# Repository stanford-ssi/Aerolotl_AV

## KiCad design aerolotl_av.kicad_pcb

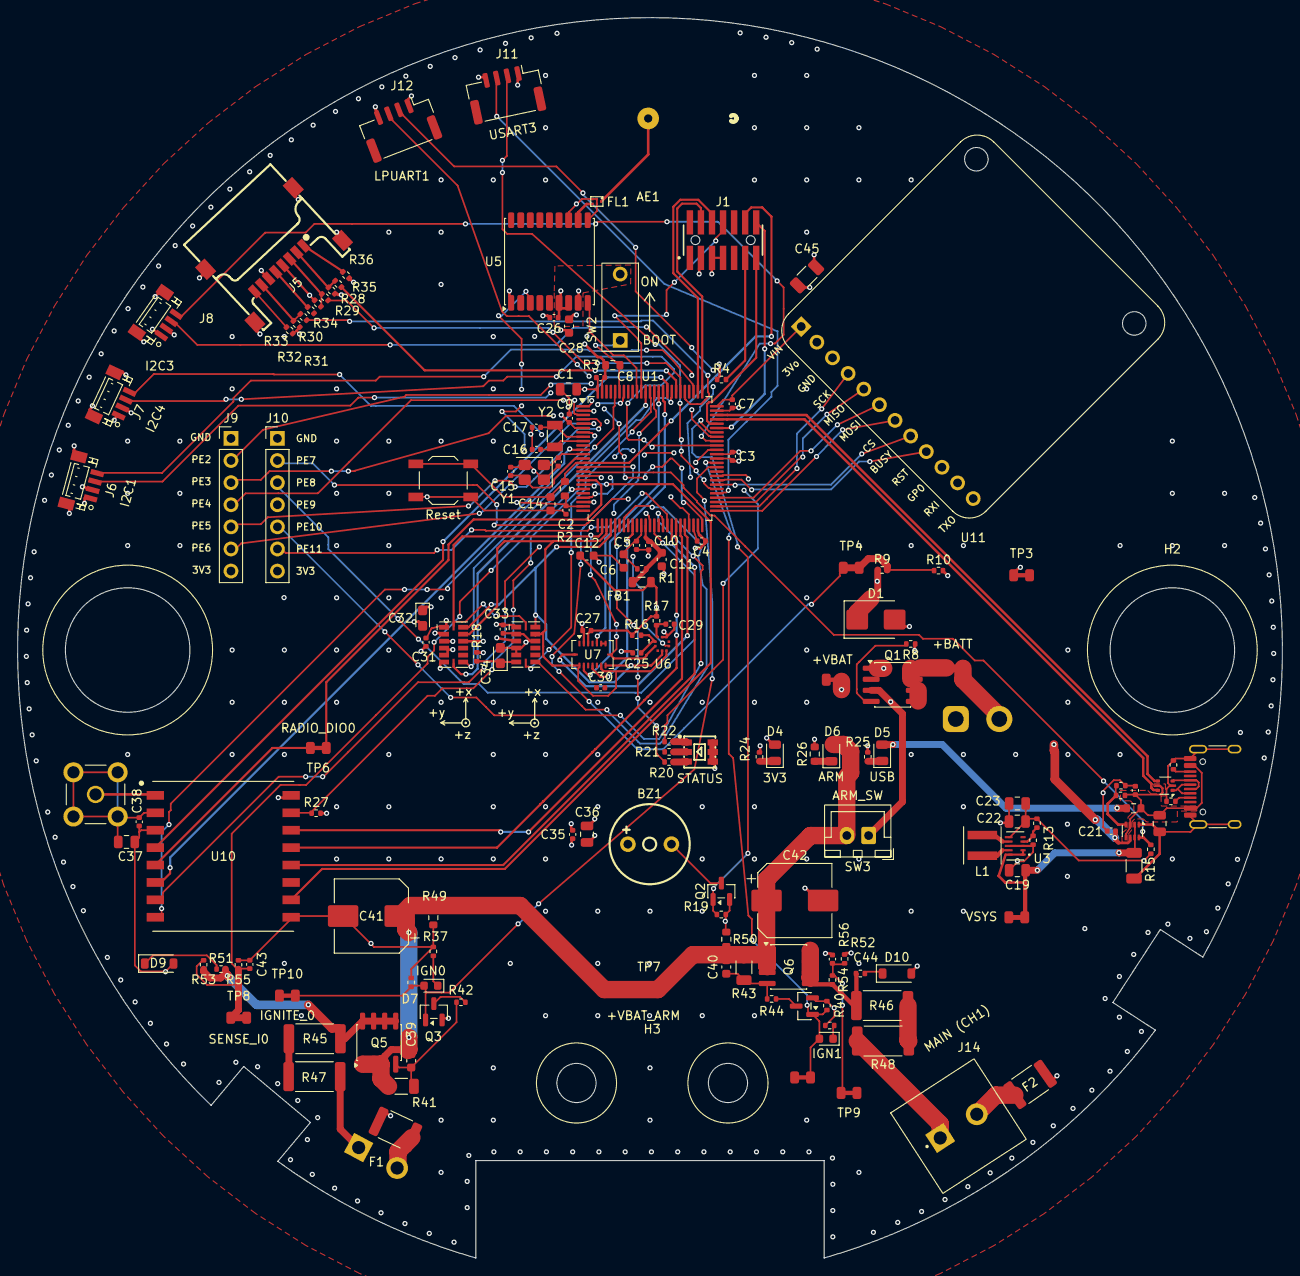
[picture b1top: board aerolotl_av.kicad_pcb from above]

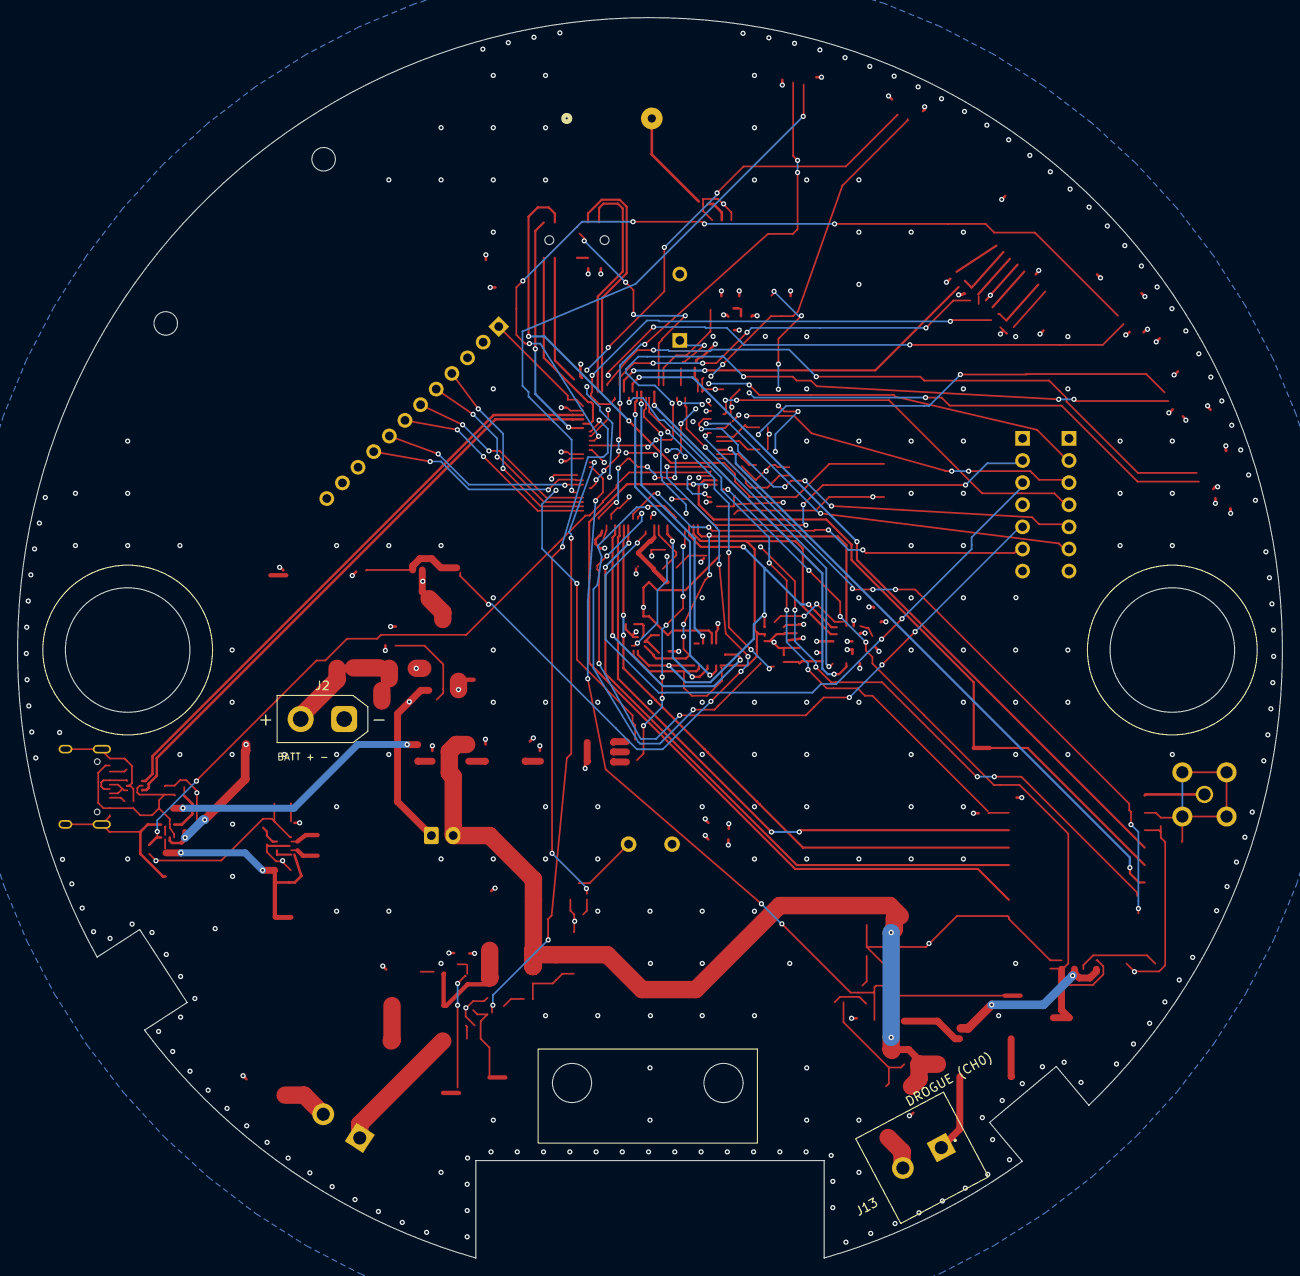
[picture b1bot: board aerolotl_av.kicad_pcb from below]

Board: 4 copper layers, 145.3 x 142.5 mm, 166 parts (2 on the bottom side), 134 nets.

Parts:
AE1: GP.1575.18.4.A.02; ANT_GP.1575.18.4.A.02_TAL
BZ1: HNB09A03; BUZ-TH_BD9.0-P5.00-D0.6-FD
C1: 4u7; C_0805_2012Metric
C2, C3, C4, C5, C7, C8, C9, C25, C26, C27, C29, C30, C31, C33, C35, C38, C43, C44: 100n; C_0402_1005Metric
C6, C11, C12: 1u; C_0603_1608Metric
C10: 10n; C_0402_1005Metric
C13, C15: 15p; C_0402_1005Metric
C14: 100n; C_0603_1608Metric
C16, C17: 4.7p; C_0402_1005Metric
C18, C19, C37: 10u; C_0805_2012Metric
C20, C21: 1u; C_0402_1005Metric
C22, C23, C36: 22u; C_0805_2012Metric
C24: 100u; C_1206_3216Metric
C28: 10u; C_0603_1608Metric
C32, C34: 1u; CP_EIA-2012-12_Kemet-R
C39, C40: 150n; C_0603_1608Metric
C41, C42: 330u; CP_Elec_8x10
C45: 47u; C_1206_3216Metric
D1: SMBJ5.0A; D_SMB
D2: STATUS; LED-SMD_RS-3535MWAR-2JYJY-J
D4: 3V3; LED_0805_2012Metric
D5: USB; LED_0805_2012Metric
D6: ARM; LED_0805_2012Metric
D7: IGN0; LED_0603_1608Metric
D8: IGN1; LED_0603_1608Metric
D9, D10: 1N4148W; D_SOD-123
F1, F2: 1812L150/24MR; Fuse_1812_4532Metric
FB1: 100; L_0805_2012Metric
FL1: B39162B4300F210; FILTER-SMD_5P-L1.4-W1.1_RSFPXXXXD
H1, H2: 3/8in rod; MountingHole_3-8in_Grommet_Heyco_G1123_D14.3mm
H3: TeleMetrum sled; TeleMetrum_Sled_Mount_2xM4
J1: SWD; STDC14_SAMTEC_FTSH-107-01-L-DV-K-A
J2: Battery (ext.); AMASS_XT30UPB-M_1x02_P5.0mm_Vertical
J3: USB_C_Receptacle_USB2.0_16P; USB_C_Receptacle_HRO_TYPE-C-31-M-12
J4: SMA; SMA_BAT-Wireless_BWSMA-KE-Z001_Vertical
J5: TF-102-15_SD_read; TF-SMD_TF-102-15
J6: I2C1; StemmaQT
J7: I2C4; StemmaQT
J8: I2C3; StemmaQT
J9: GPIO_PE2-PE6; PinHeader_1x07_P2.54mm_Vertical
J10: GPIO_PE7-PE11; PinHeader_1x07_P2.54mm_Vertical
J11: USART3; JST_GH_BM04B-GHS-TBT_1x04-1MP_P1.25mm_Vertical
J12: LPUART1; JST_GH_BM04B-GHS-TBT_1x04-1MP_P1.25mm_Vertical
J13, J14: WJ128V-5.0-2P; TerminalBlock_Kangnex_WJ128V-5.0-2P_C8269
L1: 0.47u; L_Coilcraft_XxL4020
Q1, Q5, Q6: DMP2022LSS-13; SOIC-8_3.9x4.9mm_P1.27mm
Q2, Q3, Q4: AO3400A; SOT-23
R1: 47; R_0402_1005Metric
R2, R3: 10k; R_0603_1608Metric
R4, R22, R42, R44: 100; R_0402_1005Metric
R5, R6: 5k1; R_0402_1005Metric
R7: 0R; R_0603_1608Metric
R8: 100k; R_0402_1005Metric
R9, R12, R15, R27, R32, R33, R34, R35, R36, R51, R52, R55, R56: 10k; R_0402_1005Metric
R10: 22k; R_0402_1005Metric
R11: 33k; R_0402_1005Metric
R13: 511k; R_0402_1005Metric
R14: 91k; R_0402_1005Metric
R16, R17, R18, R28, R29, R30, R31: 10; R_0402_1005Metric
R19: 3k3; R_0402_1005Metric
R20: 270; R_0402_1005Metric
R21, R37, R38: 330; R_0402_1005Metric
R24: 470; R_0402_1005Metric
R25: 910; R_0402_1005Metric
R26: 330; R_0603_1608Metric
R39, R40: 8k2; R_0402_1005Metric
R41, R43: 10k; R_1206_3216Metric
R45, R46, R47, R48: 1R; R_2512_6332Metric
R49, R50: 3k3; R_0603_1608Metric
R53, R54: 4.7k; R_0402_1005Metric
SW1: Reset; SW_SPST_TL3342
SW2: BOOT; SW_DIP_SPSTx01_Kingtek_DSWB01LHGET_W7.62mm
SW3: ARM_SW; JST_XH_B2B-XH-A_1x02_P2.50mm_Vertical
TP1: +BATT; TestPoint_KOA_RCTCTE_2.0x1.25mm
TP2: +VBAT; TestPoint_KOA_RCTCTE_2.0x1.25mm
TP3: +3V3; TestPoint_KOA_RCTCTE_2.0x1.25mm
TP4: VOLT_SENSE; TestPoint_KOA_RCTCTE_2.0x1.25mm
TP5: VSYS; TestPoint_KOA_RCTCTE_2.0x1.25mm
TP6: RADIO_DIO0; TestPoint_KOA_RCTCTE_2.0x1.25mm
TP7: +VBAT_ARM; TestPoint_KOA_RCTCTE_2.0x1.25mm
TP8: SENSE_I0; TestPoint_KOA_RCTCTE_2.0x1.25mm
TP9: SENSE_I1; TestPoint_KOA_RCTCTE_2.0x1.25mm
TP10: IGNITE_0; TestPoint_KOA_RCTCTE_2.0x1.25mm
TP11: IGNITE_1; TestPoint_KOA_RCTCTE_2.0x1.25mm
U1: STM32G473VET6; LQFP-100_14x14mm_P0.5mm
U2: USBLC6-2P6; SOT-666
U3: TPS63802DLAR; TI_VSON-HR-10_2x3mm_P0.5mm_DLA0010A
U4: TPS2116DRL; SOT-583-8
U5: MAX-M10S; ublox_MAX
U6: BMP581; LGA-10_L2.0-W2.0-P0.50-TL_BMP581
U7: BMI088; Bosch_LGA-16_4.5x3mm_P0.5mm_LayoutBorder7x1y_ClockwisePinNu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
U8: ADXL345; ADI_LGA-14_3x5mm_P0.8mm
U9: ADXL375; ADI_LGA-14_3x5mm_P0.8mm
U10: Ra-01H; Ai-Thinker_Ra-01H_SMD-16_17x16mm
U11: Airlift; Ada_Airlift
Y1: 25MHz; Crystal_SMD_3225-4Pin_3.2x2.5mm
Y2: 32.768kHz; Crystal_SMD_3215-2Pin_3.2x1.5mm

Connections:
+3.3VA: C10.1, C11.1, FB1.1, R1.1, U1.37 (VDDA)
+3V3: BZ1.1 (+), C1.1, C2.1, C3.1, C4.1, C7.1, C8.1, C9.1, C12.1, C22.1, C23.1, C26.1, C27.1, C28.1, C30.1, C31.1, C32.1, C33.1, C35.1, C36.1, C37.1, C38.1, C45.1, D2.4 (A), D2.5 (A), D2.6 (A), D4.2 (+), D9.2 (A), D10.2 (A), FB1.2, J1.03, J5.4 (VDD), J6.2, J7.2, J8.2, J9.7, J10.7, J11.4, J12.4, R2.1, R13.1, R15.1, R16.1, R17.1, R18.1, R27.1, R32.1, R33.1, R34.1, R35.1, R36.1, SW2.2 (B), TP3.1 (1_1), U1.6 (VBAT), U1.24 (VDD), U1.49 (VDD), U1.64 (VDD), U1.75 (VDD), U1.100 (VDD), U3.6 (VOUT), U5.6 (V_BCKP), U5.7 (VCC_IO), U5.8 (VCC), U7.3 (VDD), U7.11 (VDDIO), U8.1 (VDD_I/O), U8.3 (RESERVED_3), U9.1 (VDDI/O), U9.3 (RESERVED), U9.6 (VS), U10.3 (3.3V), U11.1 (VIN)
+5V: D5.2 (+), R7.1
+BATT: J2.2, Q1.5 (D), Q1.6 (D), Q1.7 (D), Q1.8 (D), TP1.1 (1_1)
+VBAT: C21.1, D1.1, Q1.1 (S), Q1.2 (S), Q1.3 (S), R9.1, SW3.1 (A), TP2.1 (1_1), U4.6 (VIN2)
+VBAT_ARM: C39.1, C40.1, C41.1, C42.1, D6.2 (+), Q5.1 (S), Q5.2 (S), Q5.3 (S), Q6.1 (S), Q6.2 (S), Q6.3 (S), R41.1, R43.1, R49.2, R50.2, SW3.2 (B), TP7.1 (1_1)
/Debugger/GNDDetect: J1.11, R4.2
/Debugger/T_NRST: C14.1, J1.12, R2.2, SW1.2, U1.14 (PG10/NRST)
/Debugger/T_SWCLK: J1.06, U1.77 (SYS_JTCK-SWCLK)
/Debugger/T_SWDIO: J1.04, U1.76 (SYS_JTMS-SWDIO)
/Debugger/T_SWO: J1.08, U1.90 (SYS_JTDO-SWO)
/Debugger/T_VCP_RX: J1.14, U1.70 (USART1_TX)
/Debugger/T_VCP_TX: J1.13, U1.71 (USART1_RX)
/External/GPIO.PE2: J9.2, U1.1 (PE2)
/External/GPIO.PE3: J9.3, U1.2 (PE3)
/External/GPIO.PE4: J9.4, U1.3 (PE4)
/External/GPIO.PE5: J9.5, U1.4 (PE5)
/External/GPIO.PE6: J9.6, U1.5 (PE6)
/External/GPIO.PE7: J10.2, U1.38 (PE7)
/External/GPIO.PE8: J10.3, U1.39 (PE8)
/External/GPIO.PE9: J10.4, U1.40 (PE9)
/External/GPIO.PE10: J10.5, U1.41 (PE10)
/External/GPIO.PE11: J10.6, U1.42 (PE11)
/External/I2C1.SCL: J6.4, U1.78 (I2C1_SCL)
/External/I2C1.SDA: J6.3, U1.94 (I2C1_SDA)
/External/I2C3.SCL: J8.4, U1.67 (I2C3_SCL)
/External/I2C3.SDA: J8.3, U1.68 (I2C3_SDA)
/External/I2C4.SCL: J7.4, U1.65 (I2C4_SCL)
/External/I2C4.SDA: J7.3, U1.66 (I2C4_SDA)
/External/LPUART1_TARGET_RX: J12.2, U1.47 (LPUART1_RX)
/External/LPUART1_TARGET_TX: J12.3, U1.50 (LPUART1_TX)
/External/USART3_TARGET_RX: J11.2, U1.56 (USART3_RX)
/External/USART3_TARGET_TX: J11.3, U1.55 (USART3_TX)
/Igniter/IGN0: D7.2 (A), Q3.1 (G), R39.1, TP10.1 (1_1), U1.61 (GPIO_Output)
/Igniter/IGN0_DRV: Q3.3 (D), R42.2
/Igniter/IGN0_HS: Q5.5 (D), Q5.6 (D), Q5.7 (D), Q5.8 (D), R45.1, R51.2, R53.1
/Igniter/IGN0_HS_GATE: C39.2, Q5.4 (G), R41.2, R42.1
/Igniter/IGN0_LED_K: D7.1 (K), R37.1
/Igniter/IGN0_OUT: J13.1, R47.2
/Igniter/IGN0_RLIM: R45.2, R47.1
/Igniter/IGN0_RTN: F1.2, J13.2
/Igniter/IGN1: D8.2 (A), Q4.1 (G), R40.1, TP11.1 (1_1), U1.62 (GPIO_Output)
/Igniter/IGN1_DRV: Q4.3 (D), R44.2
/Igniter/IGN1_HS: Q6.5 (D), Q6.6 (D), Q6.7 (D), Q6.8 (D), R46.1, R52.2, R54.1
/Igniter/IGN1_HS_GATE: C40.2, Q6.4 (G), R43.2, R44.1
/Igniter/IGN1_LED_K: D8.1 (K), R38.1
/Igniter/IGN1_OUT: J14.1, R48.2
/Igniter/IGN1_RLIM: R46.2, R48.1
/Igniter/IGN1_RTN: F2.2, J14.2
/Igniter/SENSE_I0: C43.1, R53.2, R55.1, TP8.1 (1_1), U1.20 (ADC1_IN1)
/Igniter/SENSE_I1: C44.1, R54.2, R56.1, TP9.1 (1_1), U1.21 (ADC1_IN2)
/Indicators/BUZZER: Q2.1 (G), R19.1, U1.69 (TIM1_CH1)
/Indicators/BUZZER_DRV: BZ1.2 (-), Q2.3 (D)
/Indicators/LED.B: R22.2, U1.59 (TIM4_CH1)
/Indicators/LED.G: R21.2, U1.31 (GPIO_Output)
/Indicators/LED.R: R20.2, U1.30 (GPIO_Output)
/Indicators/LED_3V3_K: D4.1 (-), R24.1
/Indicators/LED_ARM_K: D6.1 (-), R26.1
/Indicators/LED_USB_K: D5.1 (-), R25.1
/Indicators/RGB_B_K: D2.1 (K), R22.1
/Indicators/RGB_G_K: D2.2 (K), R21.1
/Indicators/RGB_R_K: D2.3 (K), R20.1
/MCU/BOOT0: R3.1, SW2.1 (A), U1.95 (PB8/BOOT0)
/MCU/GPS_RST: U1.91 (GPIO_Output), U5.9 (~RESET)
/MCU/HS_OSC_A: C13.1, U1.12 (RCC_OSC_IN), Y1.1 (OSC1)
/MCU/HS_OSC_B: C15.1, U1.13 (RCC_OSC_OUT), Y1.3 (OSC2)
/MCU/LS_OSC_A: C17.1, U1.8 (RCC_OSC32_IN), Y2.2
/MCU/LS_OSC_B: C16.1, U1.9 (RCC_OSC32_OUT), Y2.1
/MCU/PWR_STS: R15.2, U1.16 (GPIO_Input), U4.8 (ST)
/MCU/RADIO_DIO0: TP6.1 (1_1), U1.18 (GPIO_EXTI3), U10.5 (DIO0)
/MCU/RADIO_DIO1: U1.11 (GPIO_EXTI10), U10.6 (DIO1)
/MCU/RADIO_DIO2: U1.17 (GPIO_Input), U10.7 (DIO2)
/MCU/RADIO_DIO3: U1.7 (GPIO_EXTI13), U10.8 (DIO3)
/MCU/RADIO_DIO4: U1.19 (GPIO_Input), U10.10 (DIO4)
/MCU/RADIO_NSS: R27.2, U1.83 (GPIO_Output), U10.15 (NSS)
/MCU/RADIO_RST: U1.84 (GPIO_Output), U10.4 (RESET)
/MCU/SDSPI.CS: R28.1, U1.82 (GPIO_Output)
/MCU/SDSPI.MISO: R31.1, U1.80 (SPI3_MISO)
/MCU/SDSPI.MOSI: R29.1, U1.81 (SPI3_MOSI)
/MCU/SDSPI.SCK: R30.1, U1.79 (SPI3_SCK)
/MCU/SPI1.CS_345: U1.88 (GPIO_Output), U8.7 (~CS)
/MCU/SPI1.CS_375: U1.89 (GPIO_Output), U9.7 (~CS)
/MCU/SPI1.CS_BMP: U1.87 (GPIO_Output), U6.6 (CSB)
/MCU/SPI1.CS_IMU_ACC: U1.85 (GPIO_Output), U7.14 (~CSB1)
/MCU/SPI1.CS_IMU_GYRO: U1.86 (GPIO_Output), U7.5 (~CSB2)
/MCU/SPI1.INT_345: U1.32 (GPIO_EXTI0), U8.8 (INT1)
/MCU/SPI1.INT_375: U1.96 (GPIO_EXTI9), U9.8 (INT1)
/MCU/SPI1.INT_BMP: U1.33 (GPIO_EXTI1), U6.7 (INT)
/MCU/SPI1.INT_IMU_ACC: U1.46 (GPIO_EXTI15), U7.16 (INT1)
/MCU/SPI1.INT_IMU_GYRO: U1.34 (GPIO_EXTI2), U7.12 (INT3)
/MCU/SPI1.MISO: U1.28 (SPI1_MISO), U6.5 (SDO), U7.10 (SDO2), U7.15 (SDO1), U8.12 (SDO/ALT_ADDRESS), U9.12 (SDO/ALTADDRESS)
/MCU/SPI1.MOSI: U1.29 (SPI1_MOSI), U6.4 (SDI), U7.9 (SDI/SDA), U8.13 (SDA/SDI/SDIO), U9.13 (SDA/SDI/SDIO)
/MCU/SPI1.SCK: U1.27 (SPI1_SCK), U6.2 (SCK), U7.8 (SCK/SCL), U8.14 (SCL/SCLK), U9.14 (SCL/SCLK)
/MCU/SPI2.BUSY: U1.57 (GPIO_Input), U11.8 (BUSY)
/MCU/SPI2.CS: U1.51 (GPIO_Output), U11.7 (CS)
/MCU/SPI2.MISO: U1.53 (SPI2_MISO), U11.5 (MISO)
/MCU/SPI2.MOSI: U1.54 (SPI2_MOSI), U11.6 (MOSI)
/MCU/SPI2.RST: U1.58 (GPIO_Output), U11.9 (~RST)
/MCU/SPI2.SCK: U1.52 (SPI2_SCK), U11.4 (SCK)
/MCU/SPI4.MISO: U1.44 (SPI4_MISO), U10.13 (MISO)
/MCU/SPI4.MOSI: U1.45 (SPI4_MOSI), U10.14 (MOSI)
/MCU/SPI4.SCK: U1.43 (SPI4_SCK), U10.12 (SCK)
/MCU/USB_D+: U1.73 (USB_DP), U2.4 (I/O2)
/MCU/USB_D-: U1.72 (USB_DM), U2.6 (I/O1)
/MCU/VREFP: C5.1, C6.1, R1.2, U1.36 (VREF+)
/Power/BB_FB: R13.2, R14.1, U3.4 (FB)
/Power/BB_SW1: L1.1, U3.9 (L1)
/Power/BB_SW2: L1.2, U3.7 (L2)
/Power/PMUX_PR1: R11.2, R12.1, U4.4 (PR1)
/Power/P_VBUS: C18.1, C20.1, J3.A4 (VBUS), J3.A9 (VBUS), J3.B4 (VBUS), J3.B9 (VBUS), R7.2, R11.1, U2.5 (VBUS), U4.3 (VIN1), U4.5 (MODE)
/Power/RPP_GATE: Q1.4 (G), R8.1
/Power/USB_CC1: J3.A5 (CC1), R5.1
/Power/USB_CC2: J3.B5 (CC2), R6.1
/Power/USB_D_M: J3.A7 (D-), J3.B7 (D-), U2.1 (I/O1)
/Power/USB_D_P: J3.A6 (D+), J3.B6 (D+), U2.3 (I/O2)
/Power/VOLT_SENSE: R9.2, R10.1, TP4.1 (1_1), U1.15 (ADC1_IN6)
/Power/VSYS: C19.1, C24.1, TP5.1 (1_1), U3.1 (EN), U3.2 (MODE), U3.10 (VIN), U4.2 (VOUT), U4.7 (VOUT)
/SD/CARD_CS: J5.2 (CD/DAT3), R28.2, R35.2
/SD/CARD_DAT1: J5.8 (DAT1), R32.2
/SD/CARD_DAT2: J5.1 (DAT2), R36.2
/SD/CARD_MISO: J5.7 (DAT0), R31.2, R33.2
/SD/CARD_MOSI: J5.3 (CMD), R29.2, R34.2
/SD/CARD_SCK: J5.5 (CLK), R30.2
/Sensors/ADXL345_VS: C34.1, R18.2, U8.6 (VS)
/Sensors/BMP581_VDD: C29.1, R17.2, U6.10 (VDD)
/Sensors/BMP581_VDDIO: C25.1, R16.2, U6.1 (VDDIO)
/Sensors/GPS_RF_ANT: AE1.1 (1_1), FL1.1 (IN)
/Sensors/GPS_RF_IN: FL1.4 (OUT), U5.11 (RF_IN)
/Sensors/M10S.RX: U1.22 (USART2_TX), U5.3 (RXD)
/Sensors/M10S.TX: U1.25 (USART2_RX), U5.2 (TXD)
/lora/RADIO_ANT: J4.1, U10.1 (ANT)
GND: C1.2, C2.2, C3.2, C4.2, C5.2, C6.2, C7.2, C8.2, C9.2, C10.2, C11.2, C12.2, C13.2, C14.2, C15.2, C16.2, C17.2, C18.2, C19.2, C20.2, C21.2, C22.2, C23.2, C24.2, C25.2, C26.2, C27.2, C28.2, C29.2, C30.2, C31.2, C32.2, C33.2, C34.2, C35.2, C36.2, C37.2, C38.2, C41.2, C42.2, C43.2, C44.2, C45.2, D1.2, F1.1, F2.1, FL1.2 (GND), FL1.3 (GND), FL1.5 (GND), J1.05, J1.07, J2.1, J3.A1 (GND), J3.A12 (GND), J3.B1 (GND), J3.B12 (GND), J3.SH (SHIELD), J4.2, J5.6 (VSS), J5.9 (SHELL), J5.10 (SHELL), J5.11 (SHELL), J5.12 (SHELL), J6.0, J6.1, J7.0, J7.1, J8.0, J8.1, J9.1, J10.1, J11.1, J12.1, Q2.2 (S), Q3.2 (S), Q4.2 (S), R3.2, R4.1, R5.2, R6.2, R8.2, R10.2, R12.2, R14.2, R19.2, R24.2, R25.2, R26.2, R37.2, R38.2, R39.2, R40.2, R49.1, R50.1, R55.2, R56.2, SW1.1, U1.23 (VSS), U1.35 (VSSA), U1.48 (VSS), U1.63 (VSS), U1.74 (VSS), U1.99 (VSS), U2.2 (GND), U3.3 (AGND), U3.8 (GND), U4.1 (GND), U5.1 (GND), U5.10 (GND), U5.12 (GND), U6.3 (VSS), U6.8 (VSS), U6.9 (VSS), U7.2 (GNDA), U7.4 (GNDA), U7.6 (GNDIO), U7.7 (PS), U8.2 (GND), U8.4 (GND), U8.5 (GND), U8.11 (RESERVED_11), U9.2 (GND), U9.4 (GND), U9.5 (GND), U9.11 (RESERVED), U10.2 (GND), U10.9 (GND), U10.16 (GND), U11.3 (GND), Y1.2 (GND), Y1.4 (GND)
unnamed: D9.1 (K), R51.1
unnamed: D10.1 (K), R52.1

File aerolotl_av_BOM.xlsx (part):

Designators | Qty | Value | Footprint | LCSC Part | MPN | Manufacturer | Voltage | Dielectric | Tolerance | ESR / DCR | Power | JLC library | JLC stock (checked 2026-10-02 / 10-06) | Assembly | Side | Sheet | Notes / datasheet check
BZ1 |  | HNB09A03 | BUZ-TH_BD9.0-P5.00-D0.6-FD | C96102 | HNB09A03 | Huaneng |  |  |  |  |  | Extended | 44983 | JLC THT | Top | indicators | Active buzzer (internal oscillator): drive it on/off. PWM is only useful for be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
C1 |  | 4u7 | C_0805_2012Metric | C98195 | CL21B475KAFNNNE | Samsung Electro-Mechanics | 25V | X7R | 10% |  |  | Extended | 311410 | JLC SMT | Top | mcu | STM32G474 DS12288 Fig.16: VDD n x 100nF + 1 x 4.7uF
C2, C3, C4, C5, C7, C8, C9, C25, C26, C27, C29, C30, C31, C33, C35, C38, C43, C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 |  | 100n | C_0402_1005Metric | C1525 | CL05B104KO5NNNC | Samsung Electro-Mechanics | 16V | X7R | 10% |  |  | Basic | 21581667 | JLC SMT | Top | mcu | ADXL345 DS: 0.1uF ceramic at VDD I/O; ADXL375 DS: 0.1uF ceramic at VDD I/O; Ra-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
C6, C11, C12 |  | 1u | C_0603_1608Metric | C29936 | CL10B105KA8NNNC | Samsung Electro-Mechanics | 25V | X7R | 10% |  |  | Extended | 266599 | JLC SMT | Top | mcu | STM32G474 DS12288 Fig.16: VDDA 1uF; STM32G474 DS12288 Fig.16: VREF+ 100nF + 1uF
C10 |  | 10n | C_0402_1005Metric | C15195 | CL05B103KB5NNNC | Samsung Electro-Mechanics | 50V | X7R | 10% |  |  | Basic | 4033054 | JLC SMT | Top | mcu | STM32G474 DS12288 Fig.16: VDDA = 10nF + 1uF (was 100nF)
C13, C15 |  | 15p | C_0402_1005Metric | C1548 | 0402CG150J500NT | FH (Guangdong Fenghua) | 50V | C0G | 5% |  |  | Basic | 1431860 | JLC SMT | Top | mcu | HSE load cap, 12pF crystal: 2 x (12pF - ~4.5pF stray) = ~15pF
C14 |  | 100n | C_0603_1608Metric | C14663 | CC0603KRX7R9BB104 | YAGEO | 50V | X7R | 10% |  |  | Basic | 58141193 | JLC SMT | Top | mcu
C16, C17 |  | 4.7p | C_0402_1005Metric | C1569 | 0402CG4R7C500NT | FH (Guangdong Fenghua) | 50V | C0G | 0.25pF |  |  | Extended (preferred) | 597482 | JLC SMT | Top | mcu | LSE load cap for 6pF crystal: CL = C/2 + Cs (Cs ~3.5-4pF)
C18, C19, C37 |  | 10u | C_0805_2012Metric | C15850 | CL21A106KAYNNNE | Samsung Electro-Mechanics | 25V | X5R | 10% |  |  | Basic | 4951626 | JLC SMT | Top | power | Ra-01H supply decoupling (TX burst ~120mA); place at module pin 3; TPS63802 CIN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
C20, C21 |  | 1u | C_0402_1005Metric | C52923 | CL05A105KA5NQNC | Samsung Electro-Mechanics | 25V | X5R | 10% |  |  | Basic | 5613299 | JLC SMT | Top | power | TPS2116 VIN1 (VBUS) bypass; TPS2116 VIN2 (+VBAT) bypass
C22, C23, C36 |  | 22u | C_0805_2012Metric | C45783 | CL21A226MAQNNNE | Samsung Electro-Mechanics | 25V | X5R | 20% |  |  | Basic | 3990887 | JLC SMT | Top | power | TPS63802 COUT (DS 10.2.2.3: 22uF nominal, effective >= 10uF after DC bias). Two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
C24 |  | 100u | C_1206_3216Metric | C15008 | CL31A107MQHNNNE | Samsung Electro-Mechanics | 6.3V | X5R | 20% |  |  | Basic | 1940643 | JLC SMT | Top | power | TPS2116 DS 7.3.4: bulk on VOUT (VSYS) rides through the break-before-make switc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
C28 |  | 10u | C_0603_1608Metric | C19702 | CL10A106KP8NNNC | Samsung Electro-Mechanics | 10V | X5R | 10% |  |  | Basic | 10315650 | JLC SMT | Top | sensors
C32, C34 |  | 1u | CP_EIA-2012-12_Kemet-R | C444768 | TAJR105K010RNJ | Kyocera AVX | 10V | Tantalum (MnO2) | 10% | 25R @100kHz |  | Extended | 2570 | JLC SMT | Top | sensors | ADXL345 DS p.28: 1uF tantalum at VS; ADXL375 DS: 1uF tantalum at VS
C39, C40 |  | 150n | C_0603_1608Metric | C513735 | CC0603KRX7R9BB154 | YAGEO | 50V | X7R | 10% |  |  | Extended | 607110 | JLC SMT | Top | igniter | PMOS gate slow-turn-on cap across +VBAT_ARM (gate-source): 50V part, >10x margin
C41, C42 |  | 330u | CP_Elec_8x10 | C970701 | RVT1E331M0810 | DMBJ | 25V | Aluminum electrolytic | 20% | not specified (standard 105C SMD Al-El) |  | Extended | 1527 | JLC SMT | Top | igniter | Igniter reservoir on +VBAT_ARM (1S, 4.2V max). 25V part kept (already on order 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
C45 |  | 47u | C_1206_3216Metric | C96123 | CL31A476MPHNNNE | Samsung Electro-Mechanics | 10V | X5R | 20% |  |  | Basic | 296901 | JLC SMT | Top | airlift | Bulk for AirLift (ESP32) Wi-Fi TX current spikes. Place at U11 pin 1 (VIN) / pi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
D1 |  | SMBJ5.0A | D_SMB | C78423 | SMBJ5.0A | Brightking |  |  |  |  |  | Extended | 113601 | JLC SMT | Top | power | ESD / small-transient TVS only. Breakdown 6.4-7.07V is ABOVE the 6V abs max of 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
D2 |  | RS-3535MWAR-2JYJY-J | LED-SMD_RS-3535MWAR-2JYJY-J | C110402 | RS-3535MWAR | NATIONSTAR |  |  |  |  |  | Extended | 460049 | JLC SMT | Top | indicators | RS-3535MWAR common anode on +3V3. Resistors set from the datasheet V-I curve: R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
D3 |  | STM LED | LED_0805_2012Metric | C2296 | KT-0805Y | Hubei KENTO |  |  |  |  |  | Basic | 389526 | JLC SMT | Top | indicators
D4 |  | 3V3 LED | LED_0805_2012Metric | C2296 | KT-0805Y | Hubei KENTO |  |  |  |  |  | Basic | 389526 | JLC SMT | Top | indicators
D5 |  | USB LED | LED_0805_2012Metric | C2296 | KT-0805Y | Hubei KENTO |  |  |  |  |  | Basic | 389526 | JLC SMT | Top | indicators
D6 |  | ARM LED | LED_0805_2012Metric | C2296 | KT-0805Y | Hubei KENTO |  |  |  |  |  | Basic | 389526 | JLC SMT | Top | indicators
D7, D8 |  | LED red | LED_0603_1608Metric | C2286 | KT-0603R | Hubei KENTO |  |  |  |  |  | Basic | 4815898 | JLC SMT | Top | igniter
D9, D10 |  | 1N4148W | D_SOD-123 | C81598 | 1N4148W | ST(Semtech) |  |  |  |  |  | Basic | 5168664 | JLC SMT | Top | igniter
F1, F2 |  | 1812L150/24MR | Fuse_1812_4532Metric | C142805 | 1812L150/24MR | Littelfuse |  |  |  |  |  | Extended | 14071 | JLC SMT | Top | igniter
FB1 |  | 100 | L_0805_2012Metric | C1015 | GZ2012D101TF | Sunlord |  |  |  |  |  | Basic | 2341388 | JLC SMT | Top | mcu
FL1 |  | B39162B4300F210 | FILTER-SMD_5P-L1.4-W1.1_RSFPXXXXD | C2650962 | B39162B4300F210 | Qualcomm (RF360) |  |  |  |  |  | Extended | 4559 | JLC SMT | Top | sensors
J1 |  | FTSH-107-STDC14 | STDC14_SAMTEC_FTSH-107-01-L-DV-K-A | C5563894 | FTSH-107-01-L-DV-K-A | Samtec |  |  |  |  |  | Extended | 540 | JLC SMT | Top | swd
J2 |  | Battery (ext.) | AMASS_XT30UPB-M_1x02_P5.0mm_Vertical | C428721 | XT30UPB-M | Changzhou Amass Elec |  |  |  |  |  | Extended | re-check | Hand-solder (bottom side) | Bottom | power | External 1S battery (+BATT pin 1 / GND pin 2), bottom side, hand-solder. AMASS 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
J3 |  | USB_C_Receptacle_USB2.0_16P | USB_C_Receptacle_HRO_TYPE-C-31-M-12 | C165948 | TYPE-C-31-M-12 | Korean Hroparts |  |  |  |  |  | Extended | 426143 | JLC THT | Top | power
J4 |  | SMA | SMA_BAT-Wireless_BWSMA-KE-Z001_Vertical | C496549 | BWSMA-KE-Z001 | BAT WIRELESS |  |  |  |  |  | Extended | 137898 | JLC THT | Top | lora | 50 ohm. Route ANT-SMA as a short 50R coplanar trace over solid GND.
J5 |  | TF-102-15_SD_read | TF-SMD_TF-102-15 | C266609 | TF-102-15 | XUNPU |  |  |  |  |  | Extended | 19063 | JLC SMT | Top | sd
J6, J8 |  | StemmaQT | StemmaQT | C160390 | BM04B-SRSS-TB(LF)(SN) | JST |  |  |  |  |  | Extended | 52346 | JLC SMT | Top | external
J7 |  | Conn_01x04_Pin | JST_GH_BM04B-GHS-TBT_1x04-1MP_P1.25mm_Vertical | C161692 | BM04B-GHS-TBT(LF)(SN) | JST |  |  |  |  |  | Extended | 14065 | JLC SMT | Top | external
J9 |  | GPIO_PE2-PE6 | PinHeader_1x07_P2.54mm_Vertical | C492406 | PZ254V-11-07P | XFCN |  |  |  |  |  | Extended | 50677 | JLC THT | Top | external
J10 |  | GPIO_PE7-PE11 | PinHeader_1x07_P2.54mm_Vertical | C492406 | PZ254V-11-07P | XFCN |  |  |  |  |  | Extended | 50677 | JLC THT | Top | external
J11 |  | USART3 | JST_GH_BM04B-GHS-TBT_1x04-1MP_P1.25mm_Vertical | C161692 | BM04B-GHS-TBT(LF)(SN) | JST |  |  |  |  |  | Extended | 14065 | JLC SMT | Top | external
J12 |  | LPUART1 | JST_GH_BM04B-GHS-TBT_1x04-1MP_P1.25mm_Vertical | C161692 | BM04B-GHS-TBT(LF)(SN) | JST |  |  |  |  |  | Extended | 14065 | JLC SMT | Top | external
J13 |  | Screw_Terminal_01x02 | TerminalBlock_Kangnex_WJ128V-5.0-2P_C8269 | C8269 | WJ128V-5.0-02P-14-00A | KANGNEX |  |  |  |  |  | Unverified |  | Hand-solder (bottom side) | Bottom | igniter | DROGUE (CH0), bottom side, hand-solder. Fixed 2-pin screw terminal, 5.0 mm pitc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
